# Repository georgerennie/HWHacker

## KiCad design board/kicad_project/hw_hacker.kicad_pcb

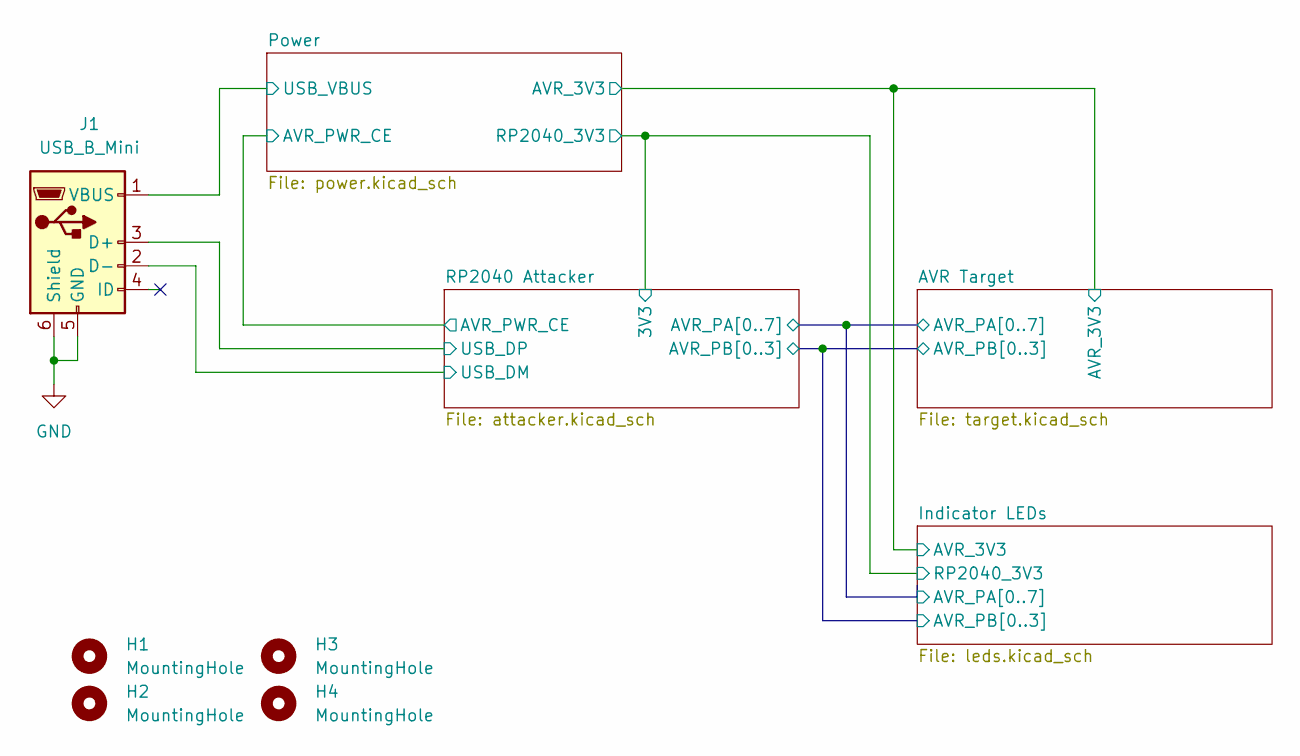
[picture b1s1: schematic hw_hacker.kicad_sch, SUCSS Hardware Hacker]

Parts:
H1, H2, H3, H4: MountingHole; MountingHole_3.2mm_M3; JLCPCB BOM 0
J1: USB_B_Mini; USB_Mini-B_Lumberg_2486_01_Horizontal; LCSC Part C91144

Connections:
/Power/USB_VBUS: J1.1 (VBUS); also elsewhere on the board
/RP2040 Attacker/USB_DM: J1.2 (D-); also elsewhere on the board
/RP2040 Attacker/USB_DP: J1.3 (D+); also elsewhere on the board
GND: J1.5 (GND), J1.6 (Shield); also elsewhere on the board

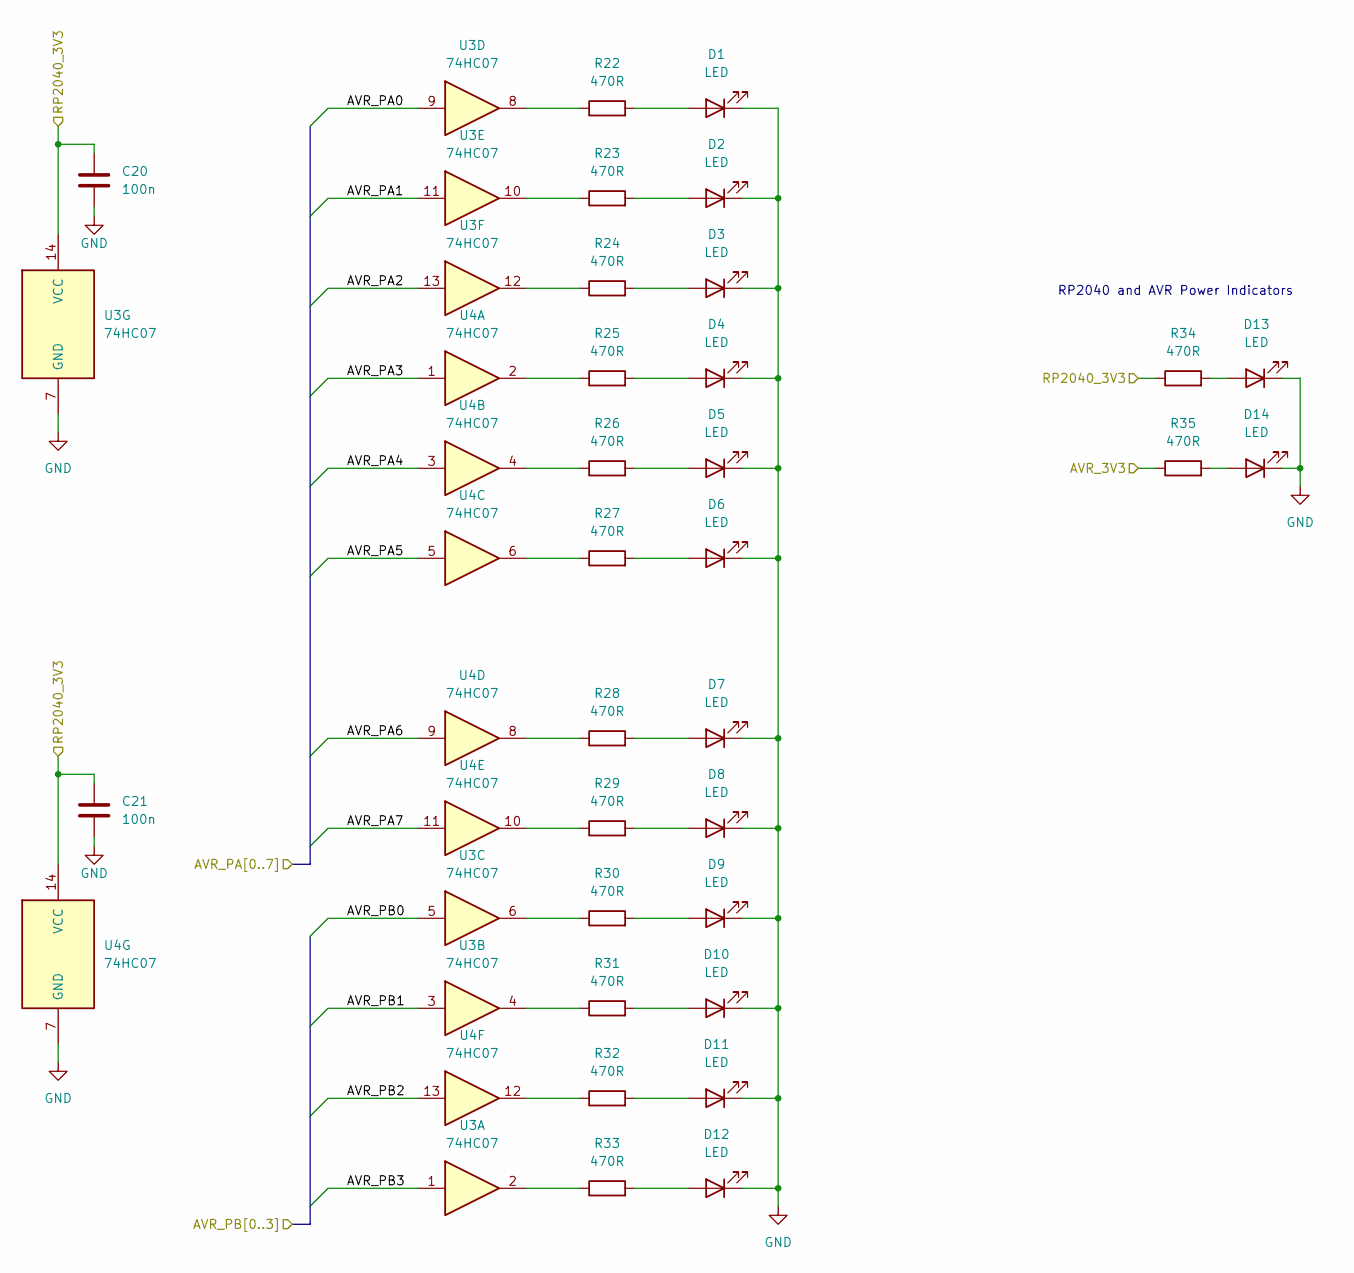
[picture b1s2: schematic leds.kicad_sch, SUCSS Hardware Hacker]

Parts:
C20, C21: 100n; C_0805_2012Metric; LCSC Part C49678
D1, D2, D3, D4, D5, D6, D7, D8, D9, D10, D11, D12, D13, D14: LED; LED_0603_1608Metric; LCSC Part C72041
R22, R23, R24, R25, R26, R27, R28, R29, R30, R31, R32, R33, R34, R35: 470R; R_0805_2012Metric; LCSC Part C17710
U3, U4: 74HC07; SOIC-14_3.9x8.7mm_P1.27mm; LCSC Part C512771

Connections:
/AVR Target/AVR_3V3: R35.1; also elsewhere on the board
/AVR Target/AVR_PA0: U3.9; also elsewhere on the board
/AVR Target/AVR_PA1: U3.11; also elsewhere on the board
/AVR Target/AVR_PA2: U3.13; also elsewhere on the board
/AVR Target/AVR_PA3: U4.1; also elsewhere on the board
/AVR Target/AVR_PA4: U4.3; also elsewhere on the board
/AVR Target/AVR_PA5: U4.5; also elsewhere on the board
/AVR Target/AVR_PA6: U4.9; also elsewhere on the board
/AVR Target/AVR_PA7: U4.11; also elsewhere on the board
/AVR Target/AVR_PB0: U3.5; also elsewhere on the board
/AVR Target/AVR_PB1: U3.3; also elsewhere on the board
/AVR Target/AVR_PB2: U4.13; also elsewhere on the board
/AVR Target/AVR_PB3: U3.1; also elsewhere on the board
/Indicator LEDs/RP2040_3V3: C20.1, C21.1, R34.1, U3.14 (VCC), U4.14 (VCC); also elsewhere on the board
GND: C20.2, C21.2, D1.1 (K), D2.1 (K), D3.1 (K), D4.1 (K), D5.1 (K), D6.1 (K), D7.1 (K), D8.1 (K), D9.1 (K), D10.1 (K), D11.1 (K), D12.1 (K), D13.1 (K), D14.1 (K), U3.7 (GND), U4.7 (GND); also elsewhere on the board
unnamed: D1.2 (A), R22.2
unnamed: D2.2 (A), R23.2
unnamed: D3.2 (A), R24.2
unnamed: D4.2 (A), R25.2
unnamed: D5.2 (A), R26.2
unnamed: D6.2 (A), R27.2
unnamed: D7.2 (A), R28.2
unnamed: D8.2 (A), R29.2
unnamed: D9.2 (A), R30.2
unnamed: D10.2 (A), R31.2
unnamed: D11.2 (A), R32.2
unnamed: D12.2 (A), R33.2
unnamed: D13.2 (A), R34.2
unnamed: D14.2 (A), R35.2
unnamed: R22.1, U3.8
unnamed: R23.1, U3.10
unnamed: R24.1, U3.12
unnamed: R25.1, U4.2
unnamed: R26.1, U4.4
unnamed: R27.1, U4.6
unnamed: R28.1, U4.8
unnamed: R29.1, U4.10
unnamed: R30.1, U3.6
unnamed: R31.1, U3.4
unnamed: R32.1, U4.12
unnamed: R33.1, U3.2

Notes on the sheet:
RP2040 and AVR Power Indicators

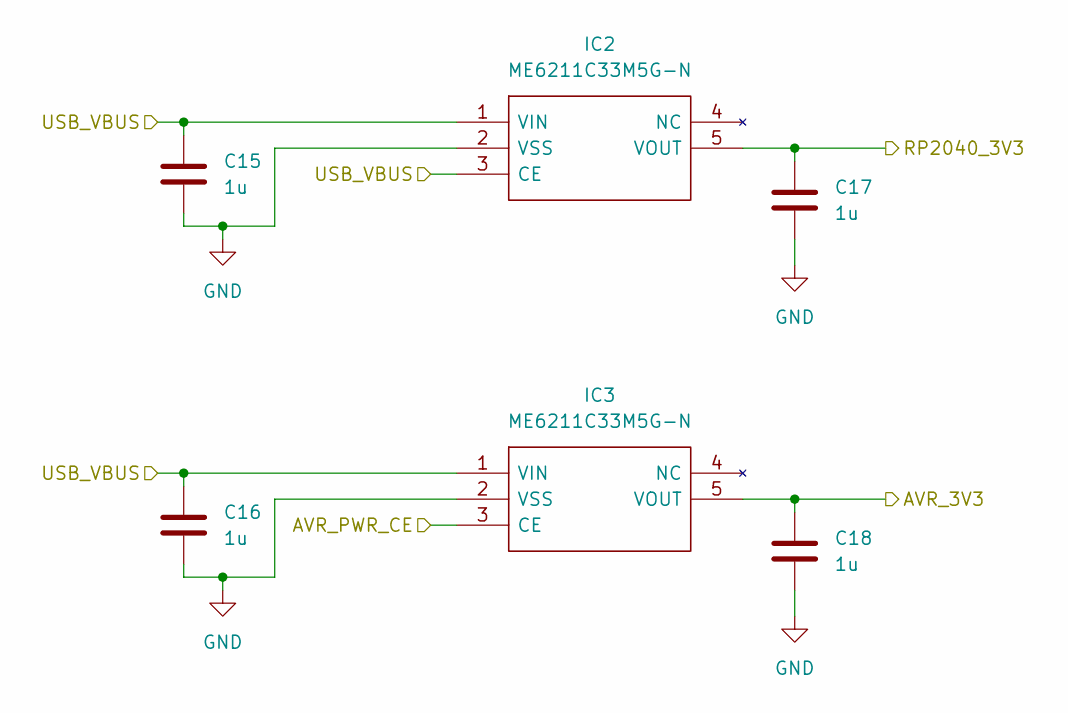
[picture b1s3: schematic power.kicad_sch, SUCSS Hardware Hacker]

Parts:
C15, C16, C17, C18: 1u; C_0805_2012Metric; LCSC Part C28323
IC2, IC3: ME6211C33M5G-N; SOT-23-5; Manufacturer_Part_Number ME6211C33M5G-N; LCSC Part C82942

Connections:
/AVR Target/AVR_3V3: C18.1, IC3.5 (VOUT); also elsewhere on the board
/Indicator LEDs/RP2040_3V3: C17.1, IC2.5 (VOUT); also elsewhere on the board
/Power/AVR_PWR_CE: IC3.3 (CE); also elsewhere on the board
/Power/USB_VBUS: C15.1, C16.1, IC2.1 (VIN), IC2.3 (CE), IC3.1 (VIN); also elsewhere on the board
GND: C15.2, C16.2, C17.2, C18.2, IC2.2 (VSS), IC3.2 (VSS); also elsewhere on the board

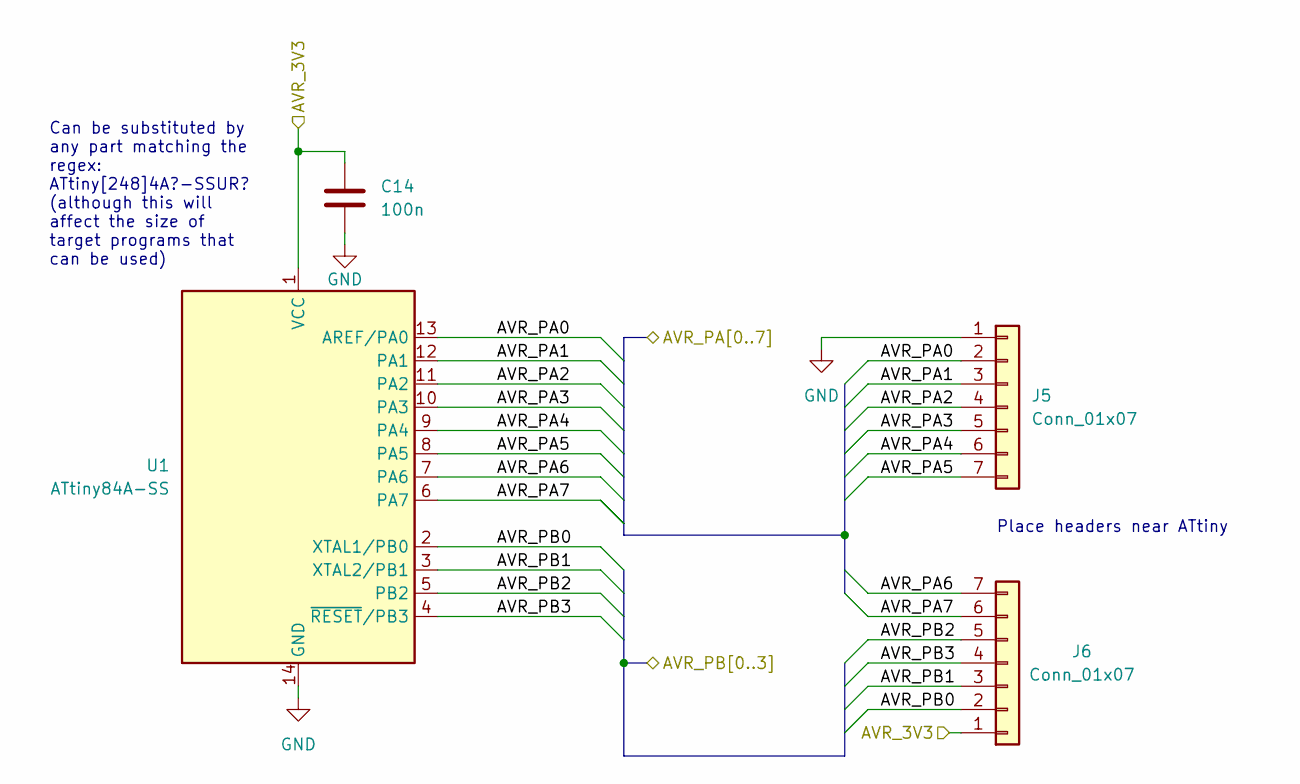
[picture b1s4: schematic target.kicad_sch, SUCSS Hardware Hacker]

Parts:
C14: 100n; C_0805_2012Metric; LCSC Part C49678
J5, J6: Conn_01x07; PinHeader_1x07_P2.54mm_Vertical; JLCPCB BOM 0
U1: ATtiny84A-SS; SOIC-14_3.9x8.7mm_P1.27mm; LCSC Part C14909

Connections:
/AVR Target/AVR_3V3: C14.1, J6.1, U1.1 (VCC); also elsewhere on the board
/AVR Target/AVR_PA0: J5.2, U1.13 (AREF/PA0); also elsewhere on the board
/AVR Target/AVR_PA1: J5.3, U1.12 (PA1); also elsewhere on the board
/AVR Target/AVR_PA2: J5.4, U1.11 (PA2); also elsewhere on the board
/AVR Target/AVR_PA3: J5.5, U1.10 (PA3); also elsewhere on the board
/AVR Target/AVR_PA4: J5.6, U1.9 (PA4); also elsewhere on the board
/AVR Target/AVR_PA5: J5.7, U1.8 (PA5); also elsewhere on the board
/AVR Target/AVR_PA6: J6.7, U1.7 (PA6); also elsewhere on the board
/AVR Target/AVR_PA7: J6.6, U1.6 (PA7); also elsewhere on the board
/AVR Target/AVR_PB0: J6.2, U1.2 (XTAL1/PB0); also elsewhere on the board
/AVR Target/AVR_PB1: J6.3, U1.3 (XTAL2/PB1); also elsewhere on the board
/AVR Target/AVR_PB2: J6.5, U1.5 (PB2); also elsewhere on the board
/AVR Target/AVR_PB3: J6.4, U1.4 (~RESET/PB3); also elsewhere on the board
GND: C14.2, J5.1, U1.14 (GND); also elsewhere on the board

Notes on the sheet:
Can be substituted by any part matching the regex: ATtiny[248]4A?-SSUR? (although this will affect the size of target programs that can be used)
Place headers near ATtiny

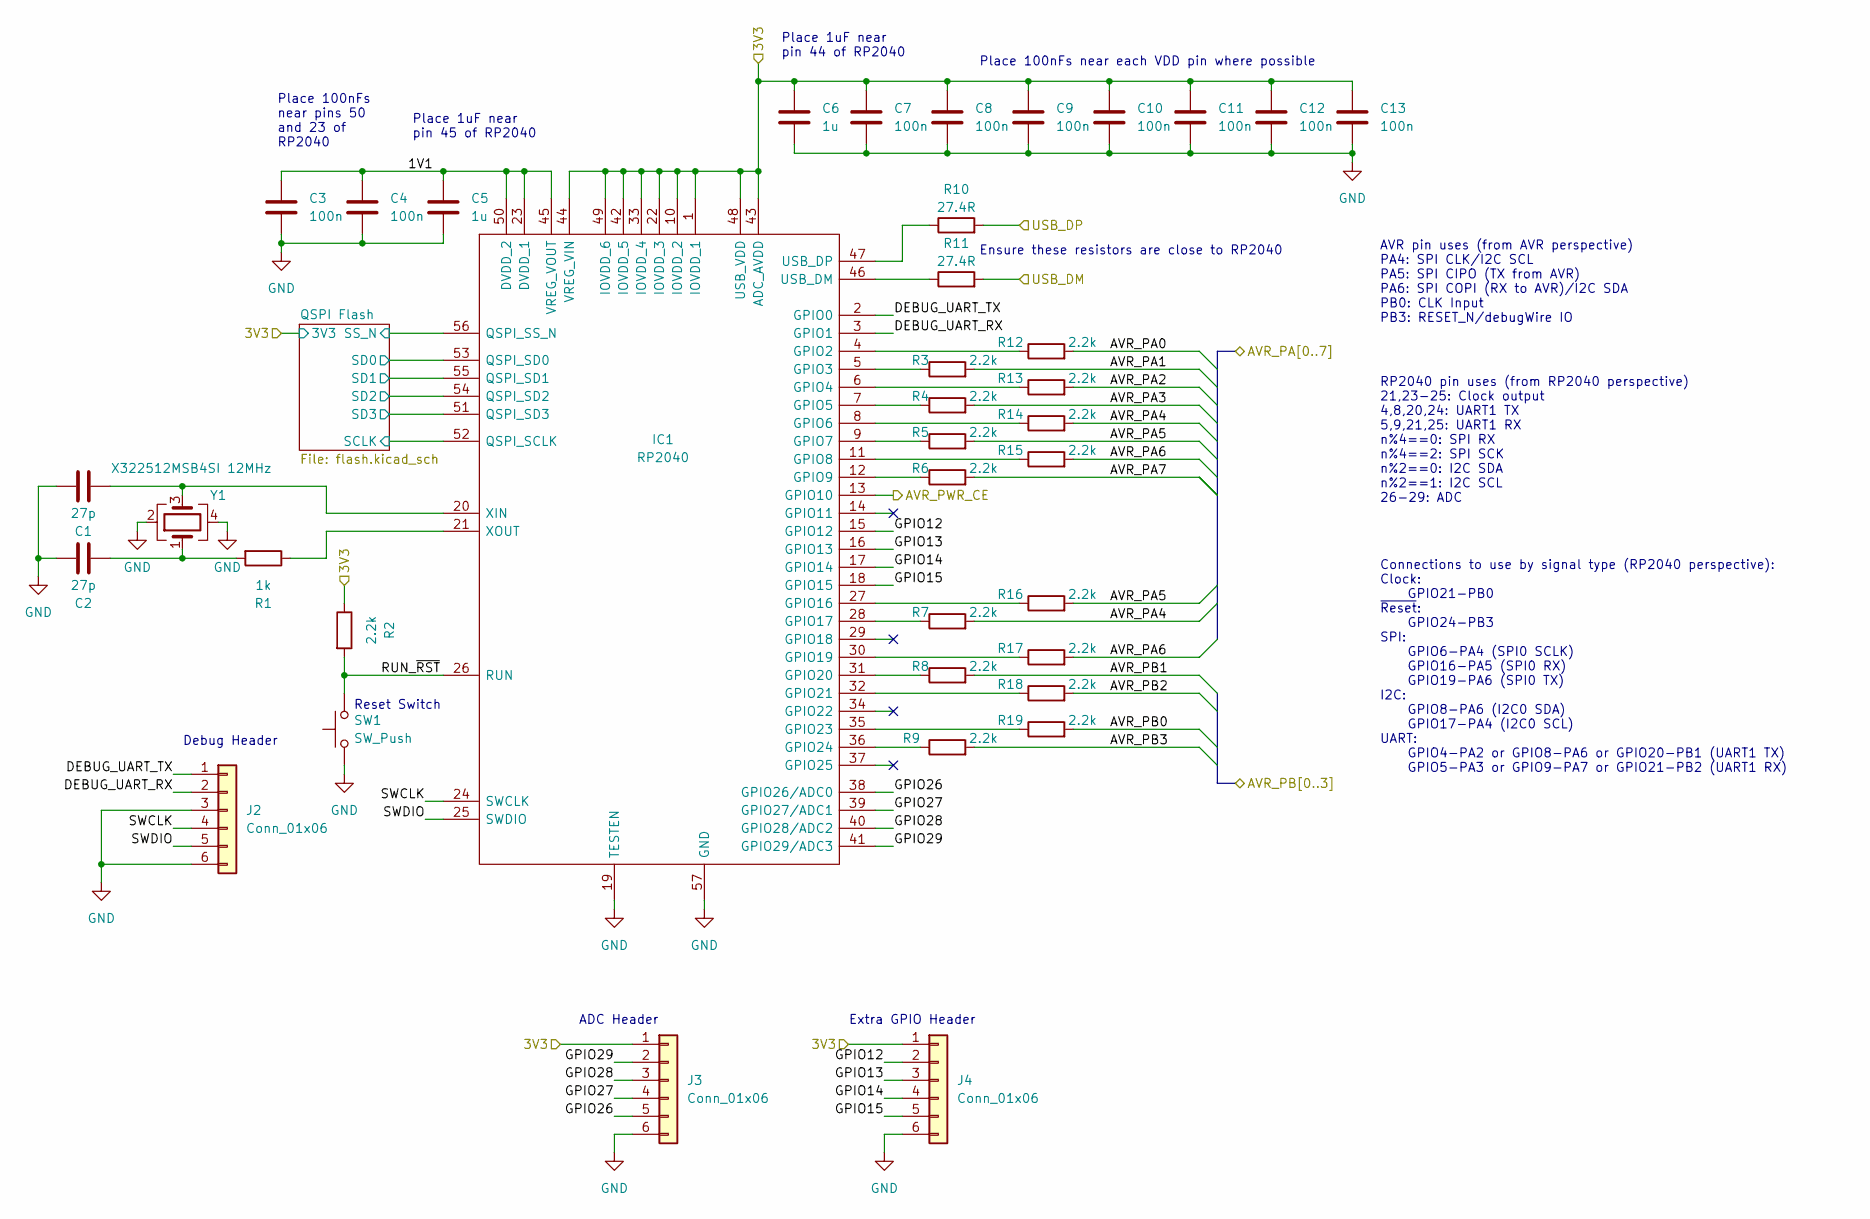
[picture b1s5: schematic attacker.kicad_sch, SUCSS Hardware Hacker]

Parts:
C1, C2: 27p; C_0402_1005Metric; LCSC Part C1557
C3, C4, C7, C8, C9, C10, C11, C12, C13: 100n; C_0402_1005Metric; LCSC Part C1525
C5, C6: 1u; C_0805_2012Metric; LCSC Part C28323
IC1: RP2040; RP2040-QFN-56; Manufacturer_Part_Number RP2040; LCSC Part C2040
J2, J3, J4: Conn_01x06; PinHeader_1x06_P2.54mm_Vertical; JLCPCB BOM 0
R1: 1k; R_0402_1005Metric; LCSC Part C11702
R2, R3, R4, R5, R6, R7, R8, R9, R12, R13, R14, R15, R16, R17, R18, R19: 2.2k; R_0603_1608Metric; LCSC Part C4190
R10, R11: 27.4R; R_0402_1005Metric; LCSC Part C172043
SW1: SW_Push; SW_SPST_SKQG_WithStem; LCSC Part C318884
Y1: X322512MSB4SI 12MHz; Crystal_SMD_3225-4Pin_3.2x2.5mm; LCSC Part C9002

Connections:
/AVR Target/AVR_PA0: R12.2; also elsewhere on the board
/AVR Target/AVR_PA1: R3.2; also elsewhere on the board
/AVR Target/AVR_PA2: R13.2; also elsewhere on the board
/AVR Target/AVR_PA3: R4.2; also elsewhere on the board
/AVR Target/AVR_PA4: R7.2, R14.2; also elsewhere on the board
/AVR Target/AVR_PA5: R5.2, R16.2; also elsewhere on the board
/AVR Target/AVR_PA6: R15.2, R17.2; also elsewhere on the board
/AVR Target/AVR_PA7: R6.2; also elsewhere on the board
/AVR Target/AVR_PB0: R19.2; also elsewhere on the board
/AVR Target/AVR_PB1: R8.2; also elsewhere on the board
/AVR Target/AVR_PB2: R18.2; also elsewhere on the board
/AVR Target/AVR_PB3: R9.2; also elsewhere on the board
/Indicator LEDs/RP2040_3V3: C6.1, C7.1, C8.1, C9.1, C10.1, C11.1, C12.1, C13.1, IC1.1 (IOVDD_1), IC1.10 (IOVDD_2), IC1.22 (IOVDD_3), IC1.33 (IOVDD_4), IC1.42 (IOVDD_5), IC1.43 (ADC_AVDD), IC1.44 (VREG_VIN), IC1.48 (USB_VDD), IC1.49 (IOVDD_6), J3.1, J4.1, R2.1; also elsewhere on the board
/Power/AVR_PWR_CE: IC1.13 (GPIO10); also elsewhere on the board
/RP2040 Attacker/1V1: C3.1, C4.1, C5.1, IC1.23 (DVDD_1), IC1.45 (VREG_VOUT), IC1.50 (DVDD_2)
/RP2040 Attacker/DEBUG_UART_RX: IC1.3 (GPIO1), J2.2
/RP2040 Attacker/DEBUG_UART_TX: IC1.2 (GPIO0), J2.1
/RP2040 Attacker/GPIO12: IC1.15 (GPIO12), J4.2
/RP2040 Attacker/GPIO13: IC1.16 (GPIO13), J4.3
/RP2040 Attacker/GPIO14: IC1.17 (GPIO14), J4.4
/RP2040 Attacker/GPIO15: IC1.18 (GPIO15), J4.5
/RP2040 Attacker/GPIO26: IC1.38 (GPIO26/ADC0), J3.5
/RP2040 Attacker/GPIO27: IC1.39 (GPIO27/ADC1), J3.4
/RP2040 Attacker/GPIO28: IC1.40 (GPIO28/ADC2), J3.3
/RP2040 Attacker/GPIO29: IC1.41 (GPIO29/ADC3), J3.2
/RP2040 Attacker/QSPI Flash/SCLK: IC1.52 (QSPI_SCLK); also elsewhere on the board
/RP2040 Attacker/QSPI Flash/SD0: IC1.53 (QSPI_SD0); also elsewhere on the board
/RP2040 Attacker/QSPI Flash/SD1: IC1.55 (QSPI_SD1); also elsewhere on the board
/RP2040 Attacker/QSPI Flash/SD2: IC1.54 (QSPI_SD2); also elsewhere on the board
/RP2040 Attacker/QSPI Flash/SD3: IC1.51 (QSPI_SD3); also elsewhere on the board
/RP2040 Attacker/QSPI Flash/SS_N: IC1.56 (QSPI_SS_N); also elsewhere on the board
/RP2040 Attacker/RUN_~RST: IC1.26 (RUN), R2.2, SW1.2
/RP2040 Attacker/SWCLK: IC1.24 (SWCLK), J2.4
/RP2040 Attacker/SWDIO: IC1.25 (SWDIO), J2.5
/RP2040 Attacker/USB_DM: R11.2; also elsewhere on the board
/RP2040 Attacker/USB_DP: R10.2; also elsewhere on the board
GND: C1.2, C2.2, C3.2, C4.2, C5.2, C6.2, C7.2, C8.2, C9.2, C10.2, C11.2, C12.2, C13.2, IC1.19 (TESTEN), IC1.57 (GND), J2.3, J2.6, J3.6, J4.6, SW1.1, Y1.2, Y1.4; also elsewhere on the board
unnamed: C2.1, R1.2, Y1.1
unnamed: IC1.4 (GPIO2), R12.1
unnamed: IC1.5 (GPIO3), R3.1
unnamed: IC1.6 (GPIO4), R13.1
unnamed: IC1.7 (GPIO5), R4.1
unnamed: IC1.8 (GPIO6), R14.1
unnamed: IC1.9 (GPIO7), R5.1
unnamed: IC1.11 (GPIO8), R15.1
unnamed: IC1.12 (GPIO9), R6.1
unnamed: IC1.27 (GPIO16), R16.1
unnamed: IC1.28 (GPIO17), R7.1
unnamed: IC1.30 (GPIO19), R17.1
unnamed: IC1.31 (GPIO20), R8.1
unnamed: IC1.32 (GPIO21), R18.1
unnamed: IC1.35 (GPIO23), R19.1
unnamed: IC1.36 (GPIO24), R9.1
unnamed: IC1.46 (USB_DM), R11.1
unnamed: IC1.47 (USB_DP), R10.1
unnamed: C1.1, IC1.20 (XIN), Y1.3
unnamed: IC1.21 (XOUT), R1.1

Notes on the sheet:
Place 1uF near pin 44 of RP2040
Reset Switch
Place 1uF near pin 45 of RP2040
Place 100nFs near each VDD pin where possible
Ensure these resistors are close to RP2040
Connections to use by signal type (RP2040 perspective): Clock: GPIO21-PB0 ~{Reset}: GPIO24-PB3 SPI: GPIO6-PA4 (SPI0 SCLK) GPIO16-PA5 (SPI0 RX) GPIO19-PA6 (SPI0 TX) I2C: GPIO8-PA6 (I2C0 SDA) GPIO17-PA4 (I2C0 SCL) UART: GPIO4-PA2 or GPIO8-PA6 or GPIO20-PB1 (UART1 TX) GPIO5-PA3 or GPIO9-PA7 or GPIO21-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
Debug Header
ADC Header
AVR pin uses (from AVR perspective) PA4: SPI CLK/I2C SCL PA5: SPI CIPO (TX from AVR) PA6: SPI COPI (RX to AVR)/I2C SDA PB0: CLK Input PB3: RESET_N/debugWire IO
Extra GPIO Header
Place 100nFs near pins 50 and 23 of RP2040
RP2040 pin uses (from RP2040 perspective) 21,23-25: Clock output 4,8,20,24: UART1 TX 5,9,21,25: UART1 RX n%4==0: SPI RX n%4==2: SPI SCK n%2==0: I2C SDA n%2==1: I2C SCL 26-29: ADC

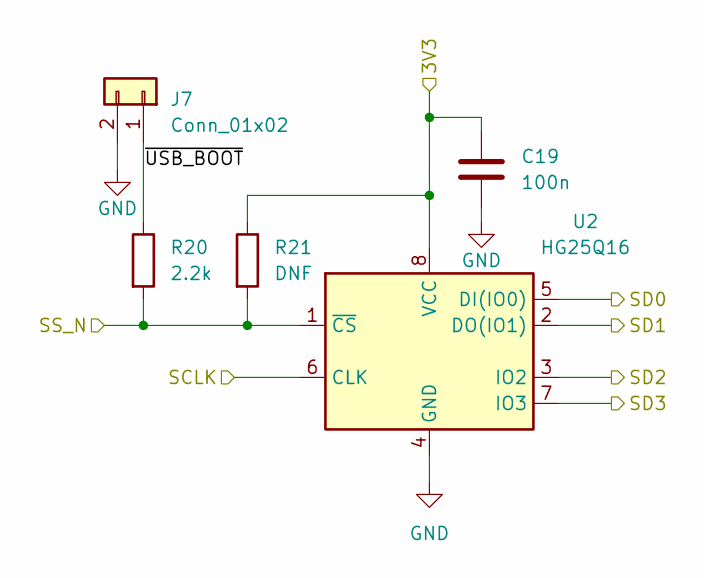
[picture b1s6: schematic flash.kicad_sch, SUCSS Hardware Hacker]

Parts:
C19: 100n; C_0805_2012Metric; LCSC Part C49678
J7: Conn_01x02; PinHeader_1x02_P2.54mm_Vertical; JLCPCB BOM 0
R20: 2.2k; R_0603_1608Metric; LCSC Part C4190
R21: DNF; R_0805_2012Metric; JLCPCB BOM 0
U2: HG25Q16; SOIC-8_5.23x5.23mm_P1.27mm; LCSC Part C2688463

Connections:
/Indicator LEDs/RP2040_3V3: C19.1, R21.1, U2.8 (VCC); also elsewhere on the board
/RP2040 Attacker/QSPI Flash/SCLK: U2.6 (CLK); also elsewhere on the board
/RP2040 Attacker/QSPI Flash/SD0: U2.5 (DI(IO0)); also elsewhere on the board
/RP2040 Attacker/QSPI Flash/SD1: U2.2 (DO(IO1)); also elsewhere on the board
/RP2040 Attacker/QSPI Flash/SD2: U2.3 (IO2); also elsewhere on the board
/RP2040 Attacker/QSPI Flash/SD3: U2.7 (IO3); also elsewhere on the board
/RP2040 Attacker/QSPI Flash/SS_N: R20.2, R21.2, U2.1 (~CS); also elsewhere on the board
/RP2040 Attacker/QSPI Flash/~USB_BOOT: J7.1, R20.1
GND: C19.2, J7.2, U2.4 (GND); also elsewhere on the board

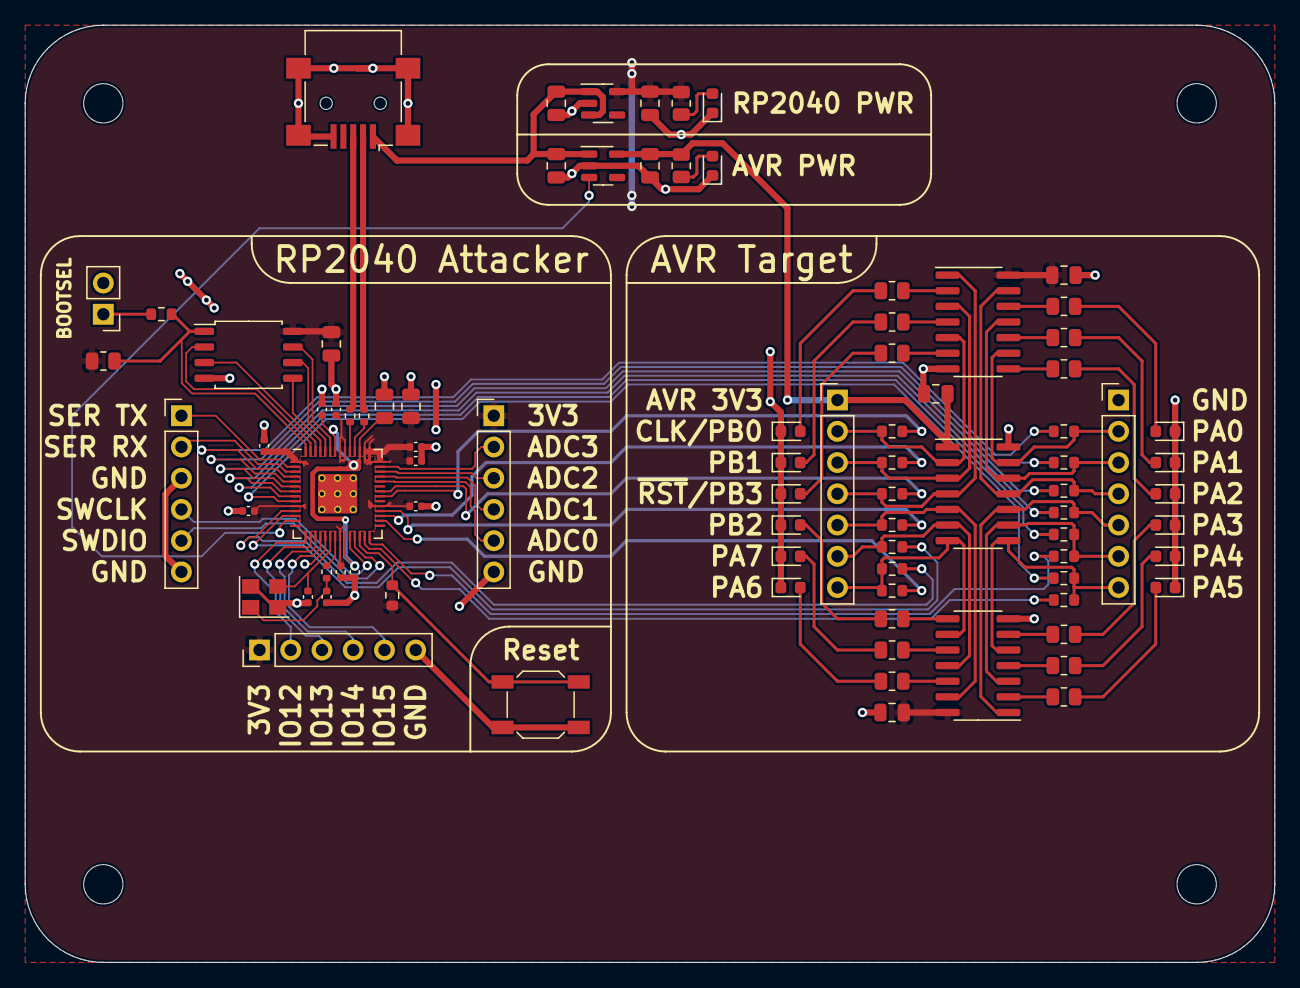
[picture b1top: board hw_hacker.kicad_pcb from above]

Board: 2 copper layers, 101.6 x 76.2 mm, 90 parts (0 on the bottom side), 86 nets.

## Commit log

2021-08-15 Initial schematic design
2021-08-22 Initial board design
2021-08-23 Fix failing DRC checks
2021-08-30 Added lcsc part numbers
2021-08-30 Initial Attacker FW
    - Rough working ISP programmer
    - Rough structure
2021-08-31 Added PIO builder submodule
2021-09-21 Started work on clock controller
2021-09-21 Update submodules
2022-02-13 Add LCSC part numbers to board file
    * Also replaced flash chip with cheaper/smaller HG25Q16 that should be
    pin compatible
2022-11-07 Update software changes
2022-11-07 Update clang-format
2022-11-07 Update to latest PIO_Builder version
2022-11-07 Formatting fixes
